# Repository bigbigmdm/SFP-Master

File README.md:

# SFP-Master

* [Installing in Linux](#installing-in-Linux)
* [Connection](#connection)
* [How to use](#how-to-use)
* [Packages](#packages)
* [Changelog](ChangeLog)
* [Licensing](#Licensing)
* [Translations](#Translations)

SFP-module data programmer for CH341a devices

**SFP-Master** is a free software programmer of optical `SFP modules` for CH341a
devices. It can be used to read, write and save SFP module data to the computer. 
The SFP-Master makes respect to [QHexEdit2](https://github.com/Simsys/qhexedit2) 
hex editor and [ch341prog](https://github.com/setarcos/ch341prog).
SFP-Master requires an SFP to I2C adapter. This adapter is used to read and 
program SFP-module data. It must be inserted into the slot labelled `24xxx` of 
the CH341a programmer.

- See more details in [SFP-Master-Hardware](https://github.com/bigbigmdm/SFP-Master-Hardware)
repository.

The OSHWLAB project of this adapter is [here](https://oshwlab.com/einkreader/ch341a_sfp_adapter).

Jumpers J1 to J3 (TxPWR, RxPWR, TxEN) must be installed initially. They are used
to supply power to the SFP module. If you want to program a module with 
hardware write protection, remove one of the jumpers and try to program 
the module. 
If it fails, remove the other jumper and repeat the operation.

# Installing in Linux

For build are needed:
- g++ or clang
- CMake
- libusb 1.0
- Qt5 or QT6
- Qt5 Qt5LinguistTools or QT6 Qt5LinguistTools
- pkgconf or pkg-config
- udev

On Debian and derivatives for QT5 version:

`sudo apt-get install cmake g++ libusb-1.0-0-dev pkgconf qtbase5-dev qttools5-dev`

On Debian and derivatives for QT6 version:

`sudo apt-get install cmake g++ libusb-1.0-0-dev pkgconf qt6-base-dev 
qt6-tools-dev linguist-qt6 qt6-l10n-tools qt6-tools-dev-tools`

On Debian >=13 and Ubuntu >=23.10:

`sudo apt-get install systemd-dev`

On older:

`sudo apt-get install udev`

To build and install the SFP-Master enter:

`sudo ./build_all.sh`

To uninstall, enter:

`sudo ./uninstall.sh`

### [Install](https://hu.blackpanther.hu/alkalmazas-letoltes/sfp-modul-olvaso-iro-mester-flasher/) to blackPanther OS

`installing sfp-master`

# Connection

To work with the programmer, connect the SFP module to the connector in the SFP
 adapter, connect the SFP adapter to the CH341A programmer device to the slot 
 marked `24xx`. Connect the CH341A Programmer Unit to the USB connector of the
 computer and start the `SFP-Master` program.

# How to use
The hexadecimal chip editor (right side of the screen) is used to display and 
modify buffer data.

It contains the following controls: `Hex-Editor / Undo` or 
 or `<Ctrl+Z>` undo and 
`Hex-Editor / Redo` or  or `<Ctrl+Y>` redo.

- Pressing `SFP-module / Read from SFP` or  or `<Ctrl+R>`
 to read data from the SFP-module into the computer buffer.
- Pressing `SFP-module / Write to SFP` or  or `<Ctrl+W>`
 to write data from the 
computer buffer into the SFP-module.
- Press `SFP Module / Set Module Password` or  or
 `<Ctrl+P>` to bring up the password setting menu for modules that are password 
 protected.
- Press `SFP Module / Scan Module Password` or  or
 `<Ctrl+Shift+P>` for scan known factory/vendor SFP write-unlock passwords. 
 These are published defaults for modules, not credentials for anyone 
 else's hardware.
- The checkboxes are used to select the address area for read, write or save
 procedures:
 
|  Checkbox colour  | SFP-Master address | Real SFP address |
| :---              |       :---:        |       :---:      |
| Green (Always on) |   0x0000 - 0x007F  |  0xA000 - 0xA07F |
| Blue              |   0x0080 - 0x00FF  |  0xA080 - 0xA0FF |
| Red               |   0x0100 - 0x017F  |  0xA200 - 0xA27F |
| Yellow            |   0x0180 - 0x01FF  |  0xA280 - 0xA2FF |

The `Parse` button is used to re-parse hexadecimal data in the hex editor, if 
they have been changed manually.

The `Checksum` button is used to calculate two checksums (addresses 0x03F and 
0x05F according to SFF-8472 Rev 12.3), 
if the module data have been changed manually in the hex editor.

Changing the data on the left side of the screen automatically causes the data 
to be changed in the hex editor.

- The `File / Save` or  or `<Ctrl+S>` button is used to 
save the computer buffer to a file.
- The `File / Open`  or  or `<Ctrl+O>` button is used to 
save the file in the computer buffer.
- The `File / Exit`  or  or `<Ctrl+X>` button is used to 
close the program. 

## Packages

- For some versions of Fedora, you can use the COPR repositories.
```
sudo dnf install dnf-plugins-core
sudo dnf copr enable bigmdm/sfp-master
sudo dnf install sfp-master
``` 
- For some versions of UBUNTU, you can use the Launchpad repositories.
```
sudo add-apt-repository ppa:bigmdm/sfp-master
sudo apt update
sudo apt install sfp-master
``` 

- The `ARCH AUR repository` by [Giovanni Scafora](https://github.com/giovanni69) is [here](https://aur.archlinux.org/packages/sfp-master-git)

- The Windows release by [Anime4000](https://github.com/Anime4000) is [here](https://github.com/Anime4000/SFP-Master/releases)

## Licensing

Copyright (C) 2024 - 2025 Mikhail Medvedev. 
This project and [ch341prog](https://github.com/setarcos/ch341prog) use 
[GPL-3+ License](https://www.gnu.org/licenses/gpl-3.0.html), 
some parts taken from project [QHexEdit2](https://github.com/Simsys/qhexedit2) 
is [LGPL-2.1](https://www.gnu.org/licenses/old-licenses/lgpl-2.1.html). 

## Translations

- Italian translation by [Giovanni Scafora](https://github.com/giovanni69)

- Hungarian translation by [Charles K Barcza](https://github.com/blackPantherOS)

- Brasil translation by [Alexandre C. Leite](https://github.com/alexandrecleite)

- German translation by [Wucke13](https://github.com/wucke13)

- Simplified Chinese translation by [taotieren](https://github.com/taotieren)

Anyone can add or improve a translation by making a pull request.
Translations files are located in:
[language/](https://github.com/bigbigmdm/SFP-Master/tree/main/language) 

You can also add translation to the desktop file ([SFP-Master.desktop](https://github.com/bigbigmdm/SFP-Master/blob/main/other/SFP-Master.desktop)).

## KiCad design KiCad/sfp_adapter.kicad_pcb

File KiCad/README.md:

# KiCad files

| KiCad render | Assembled product |
|:------------:|:-----------------:|
|  |  |

## BOM

| Molex  | 74441-0001 |
|--------|------------|
| Molex  | 74737-0009 |

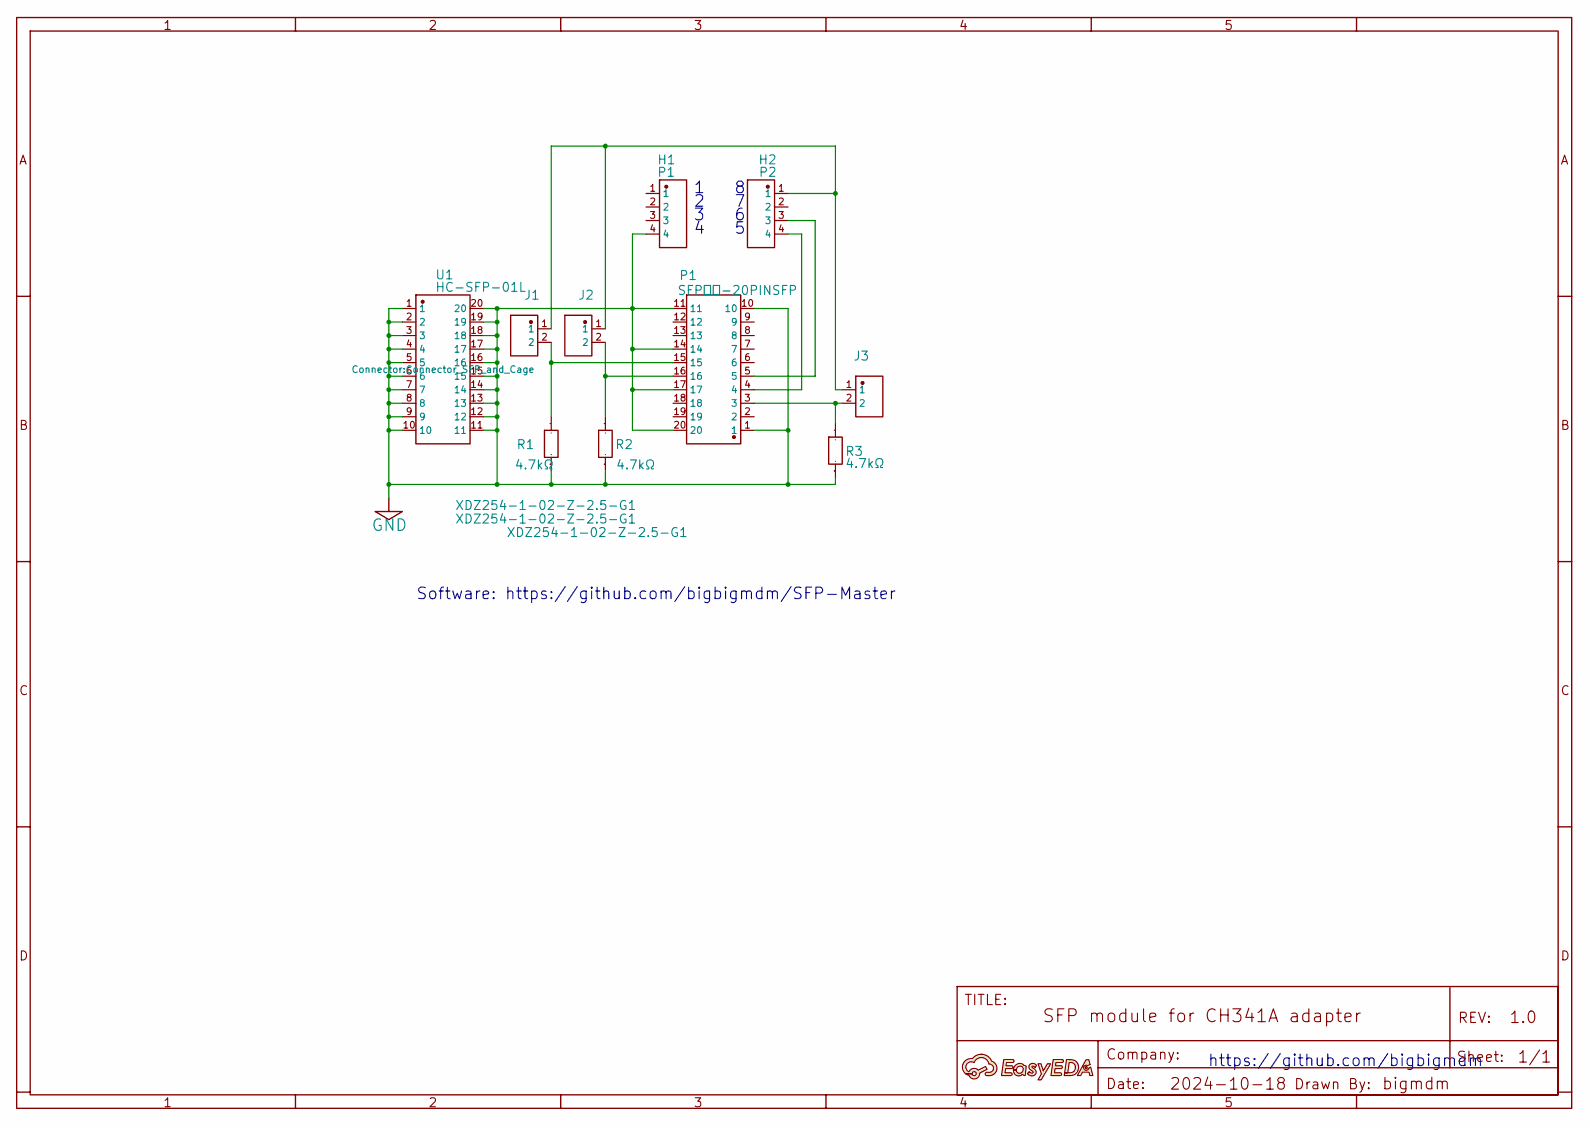
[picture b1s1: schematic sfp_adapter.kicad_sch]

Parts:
A1: A; Manufacturer Part ?
H1: P1; PinHeader_1x04_P2.54mm_Vertical; Manufacturer Part PZ254V-11-04P
H2: P2; PinHeader_1x04_P2.54mm_Vertical; Manufacturer Part PZ254V-11-04P
J1, J2, J3: XDZ254-1-02-Z-2.5-G1; PinHeader_1x02_P2.54mm_Vertical; Manufacturer Part XDZ254-1-02-Z-2.5-G1
P1: SFP插座-20PINSFP; CONN-SMD_SFP-20PIN; Manufacturer Part SFP插座-20PINSFP
R1, R2, R3: 4.7kΩ; R_0805_2012Metric; Manufacturer Part 0805 ±1% 4K7
U1: HC-SFP-01L; Connector_SFP_and_Cage; Manufacturer Part HC-SFP-01L

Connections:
GND: H1.4 (4_4), P1.1, P1.10, P1.11, P1.14, P1.17, P1.20, R1.1, R2.1, R3.1, U1.1, U1.2, U1.3, U1.4, U1.5, U1.6, U1.7, U1.8, U1.9, U1.10, U1.11, U1.12, U1.13, U1.14, U1.15, U1.16, U1.17, U1.18, U1.19, U1.20
unnamed: H2.1, J1.1, J2.1, J3.1
unnamed: H2.3, P1.5
unnamed: H2.4, P1.4
unnamed: J1.2, P1.15, R1.2
unnamed: J2.2, P1.16, R2.2
unnamed: J3.2, P1.3, R3.2

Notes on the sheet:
Software: https://github.com/bigbigmdm/SFP-Master
https://github.com/bigbigmdm

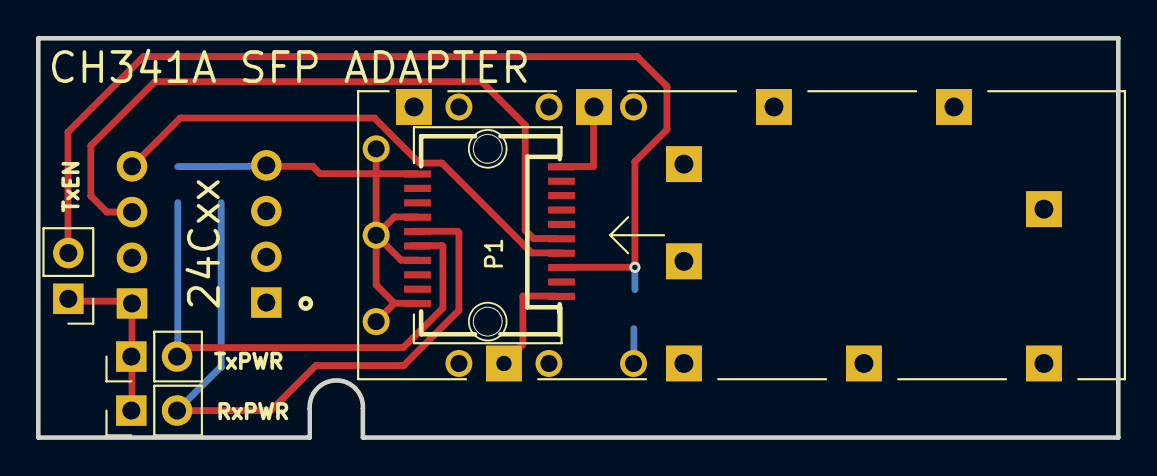
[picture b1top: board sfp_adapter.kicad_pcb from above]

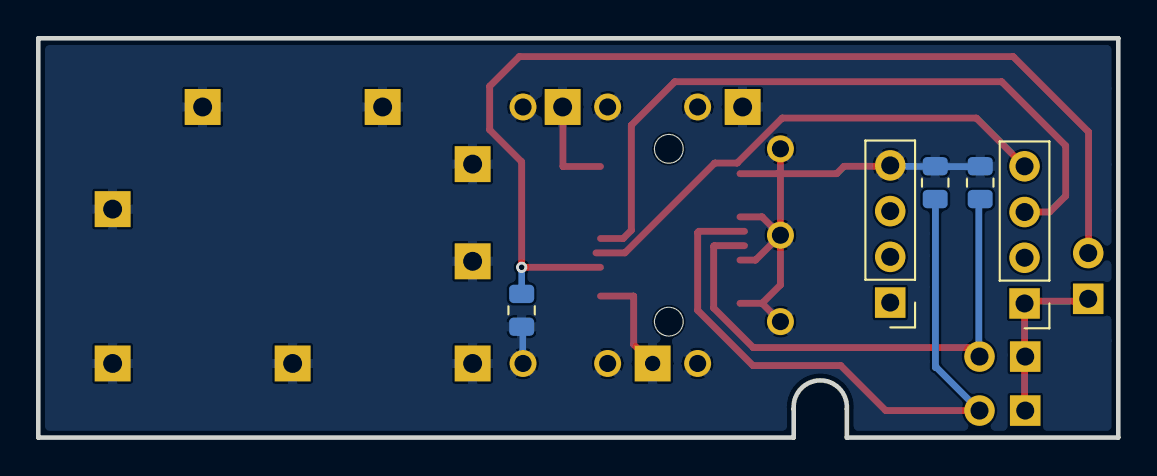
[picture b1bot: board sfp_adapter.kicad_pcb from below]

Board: 2 copper layers, 60.0 x 22.2 mm, 10 parts (5 on the bottom side), 7 nets.

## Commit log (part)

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2024-12-03 Initial upload
2024-12-03 Image corrected
2024-12-03 Unused components removed
2024-12-04 Status of programmer added, hexedit resize added
2024-12-05 Action exit added
2024-12-05 About/url changed
2024-12-05 Help contexts added to the main form
2024-12-07 Line lenght 9/25 in meter added
2024-12-09 Manuals added
2024-12-09 Metainfo file added
2024-12-09 Translations added
2024-12-10 pdf help added
2024-12-10 Fix: uncorrect Spanish translations
2024-12-10 Fedora spec file added
2024-12-10 Italian Translation added
2024-12-10 photos added
2024-12-10 Photo added
2024-12-10 Italian translations included
2024-12-10 Sections added
2024-12-10 Italian language added
2024-12-10 Fix: richtext parsing errors
2024-12-12 Fix: rpm building errors
2024-12-12 Fix: building errors
2024-12-12 Fix: translation error
2024-12-12 license added
2024-12-12 Create changelog
2024-12-12 add sections
2024-12-12 Fix uncorrected text
2024-12-12 New version added
2024-12-13 Additional templates added
2024-12-13 Address table added
2024-12-13 Small improvements to the interface
2024-12-13 Fix: incorrect height of checkboxes
2024-12-13 Removed unnecessary variables
2024-12-14 Add Hungarian lang support
2024-12-14 Update translations
2024-12-14 Update Hungarian translation
2024-12-17 debian folder added
2024-12-17 Prepared a new release
2024-12-17 Changelog updated
2024-12-17 fix debian package reeors
2024-12-17 Bugfix: rule conflicts with IMSProg package
2024-12-17 fix debian package errors
2024-12-18 Fix: spelling error
2024-12-18 Optimization for Ubuntu and Debian
2024-12-18 Changing format of document
2024-12-18 Initial release changed
2024-12-18 Added information about Ubuntu package
2024-12-18 Update README.md
    Add install and translator info
2024-12-19 Brasil translation added
2024-12-22 Improvements to the Italian translation
2024-12-22 Arch AUR repository added
2024-12-22 moving therepology block
2024-12-22 Other minor improvements to the Italian translation
2024-12-22 Corrected spelling errors
2024-12-30 Long lines removed
2024-12-30 Prepared release 1.0.4
2025-01-05 feat: add German translation
    The only thing that I'm unhappy about is translating vendor to Anbieter,
    that might or might not catch the original intent well.
2025-01-05 Fix uncorrect xml header
2025-01-05 Added German translation
2025-01-08 Fixed small GUI bugs
2025-01-08 Preparing a new version
2025-02-05 Changed License from GPL2 to GPL3
2025-02-05 Trailing spaces have been removed.
2025-03-03 Memory leaks fixed
2025-03-04 Memory leaks fixed variant two
2025-03-07 Fix:wrong header
2025-03-31 The Windows release added
2025-06-24 Closed bug 1108245
2025-06-24 Fixed weekday
2025-06-24 Standard changed
2025-06-24 Fix: incorrect tagname
2025-06-24 sfp-master.spec excluded
2025-06-24 The file other/SFP-Master.pdf has been removed from the project
2025-08-25 Bump actions/checkout from 4 to 5
    Bumps [actions/checkout](https://github.com/actions/checkout) from 4 to 5.
    - [Release notes](https://github.com/actions/checkout/releases)
    - [Changelog](https://github.com/actions/checkout/blob/main/CHANGELOG.md)
    - [Commits](https://github.com/actions/checkout/compare/v4...v5)
    ---
    updated-dependencies:
2025-09-10 Preparing to migration from Qt5 to Qt6
2025-09-10 Fix: broken link
2025-09-10 Universal QT5/QT6 version
2025-09-11 Fix:uncompatible with Ubuntu 20.04 version of QT5
2025-09-11 Preparing a new release
2025-09-11 Preparing version 1.0.7
2025-09-12 Fix:wrong lrelease version
2025-11-10 update sfp-master zh-hans
2025-11-24 Bump actions/checkout from 5 to 6
    Bumps [actions/checkout](https://github.com/actions/checkout) from 5 to 6.
    - [Release notes](https://github.com/actions/checkout/releases)
    - [Changelog](https://github.com/actions/checkout/blob/main/CHANGELOG.md)
    - [Commits](https://github.com/actions/checkout/compare/v5...v6)
    ---
    updated-dependencies:
2025-12-04 Small fix to the Italian translation
2026-04-13 I2C driver changed
2026-04-14 Fix: UDEV and LIBUSB pathes, used PKGCONFIG
2026-04-14 Unused variables removed
2026-04-14 Mutliplatform translation path added
2026-04-14 Translations updated
2026-04-14 Prepared a new version
2026-04-15 Unused files removed
2026-04-16 Qt version switch added
2026-04-16 Added Qt version switch
2026-04-16 Deprecated images removed
2026-04-16 Update build matrix to remove Ubuntu-20
    Removed Ubuntu-20 from the build matrix in GitHub Actions.
2026-04-16 Depends changed from Qt5 to Qt6
2026-04-16 Restore libraries
2026-04-23 Standaed version changed
2026-04-23 lintian-overrides added
2026-04-23 trailing-whitespace removed
2026-06-22 Bump actions/checkout from 6 to 7
    Bumps [actions/checkout](https://github.com/actions/checkout) from 6 to 7.
    - [Release notes](https://github.com/actions/checkout/releases)
    - [Changelog](https://github.com/actions/checkout/blob/main/CHANGELOG.md)
    - [Commits](https://github.com/actions/checkout/compare/v6...v7)
    ---
    updated-dependencies:
